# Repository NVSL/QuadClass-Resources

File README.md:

# The Quadcopter Class

Welcome to CSE176e Robotic System Design and Implementation (AKA, the Quadcopter Class).

This repo serves an the homepage for the course labs. It contains all
the lab write ups and several resources you will use throughout the
course.

- `labs` has all the labs. The write ups reference the starter repos they use.
- `Fusion 360` has the pre-built parts library, CAM files, and design rule files to use with Fusion 360.
- `Lecture Slides` has slides that aren't part of any particular lab.

Please see the [course home page](https://sites.google.com/ucsd.edu/the-quadcopter-class/home) or the [class calendar](ohttps://docs.google.com/spreadsheets/d/1cgSJm-5A6JrrA-iNKX8d2A0SE1PBk1CwzLvdhLKHuWY/) for schedule, due dates, and other logistical issues.

## A Note About Software Tool Names

The PCB design software we use is called Fusion 360. It used to be known as "Eagle". I've mostly updated the course materials to reflect this change.  If you see "Eagle" you should think "Fusion 360".

## Overview

We are going to build remote-controlled quadcopters from scratch in 10 weeks.

The goals for the course are for you to learn how to design, assemble, and program a moderately complex electronic device. The device you will build is a small, remote-controlled quadcopter similar to this:

In particular, you'll learn and/or practice these skills/topics:

- Printed circuit board design
  - Implementing a spec
  - Leveraging reference designs
  - Interpreting data sheets
  - Selecting parts
- PCB Assembly
  - Concepts
  - Moderately advanced soldering
- Embedded Systems Programming
  - Real-time
  - Resource constrained
- Basic Sensor fusion
- Basic Control Theory

## Labs

There are 10 labs divided into four sections. Deadlines are on the course homepage.

The slides for each lab are in the directory with the lab description.

### PCB Design

1. [Introduction To Fusion 360](https://github.com/NVSL/QuadClass-Resources/tree/master/labs/Introduction-To-Eagle)
2. [Building Parts In Fusion 360](https://github.com/NVSL/QuadClass-Resources/tree/master/labs/Building-Parts-In-Eagle)
3. [Building The Quadcopter Schematic](https://github.com/NVSL/QuadClass-Resources/tree/master/labs/Building-The-Quadcopter-Schematic)
4. [Laying Out The Board](https://github.com/NVSL/QuadClass-Resources/tree/master/labs/Laying-Out-The-Board)
5. [Manufacturing The Board](https://github.com/NVSL/QuadClass-Resources/tree/master/labs/Manufacturing-The-Board)

### PCB Assembly

6. [Assembling A PCB](https://github.com/NVSL/QuadClass-Resources/tree/master/labs/Assembling-A-PCB)

### Software

7. [Programming The Hardware](https://github.com/NVSL/QuadClass-Resources/tree/master/labs/Programming-The-Hardware)
8. [Sensing and Control](https://github.com/NVSL/QuadClass-Resources/tree/master/labs/Sensing-And-Control)
<!-- 8. [Sensing and Filtering](https://github.com/NVSL/QuadClass-Resources/tree/master/labs/Sensing-And-Filtering)-->
<!-- 9. [Implementing PID](https://github.com/NVSL/QuadClass-Resources/tree/master/labs/Implementing-PID)-->

### Flight

9. [Flight](https://github.com/NVSL/QuadClass-Resources/tree/master/labs/Flight)
10. [Cleanup](https://github.com/NVSL/QuadClass-Resources/tree/master/labs/Cleanup)

## Lab Equipment

The course requires several pieces of equipment:

1. A remote control.
2. A PID test stand.
3. A quadcopter prototype.
4. Miscelleneous cables, parts, etc.

You will also build a quadcopter, which you can also keep.

### Keeping the Remote

You cannot keep the remote you used in class. However, I a limited number of older remote boards that you can have if you really want one. Please talk to me near the end of the course, if you are interested.

### Returning the Equipment

The PID test stand, flight control board, remote, and other miscelleneous equipment you borrow for the labs must be returned or replaced (modulo normal wear and tear) before I will assign you a grade in the course.

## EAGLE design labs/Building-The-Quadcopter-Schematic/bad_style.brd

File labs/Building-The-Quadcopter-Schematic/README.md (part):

# Assembling The Quadcopter Schematic

To be completed in pairs.

Check course schedule for the due dates.

## Skills to Learn

1. Design a schematic to match a written specification.
2. Integrate portions of a reference design into your schematic.
3. Read and understand key portions of part datasheets.

## Equipment, Supplies, and Software You Will Need

1. Create a team in eaglint. You _must_ do this before clicking the starter link below.
1. The repo you started in "Programming the Hardware Lab"
1. The `custom.lbr` library you built in previous lab, OR your cloud save for the custom library. From here on out, maintain copies of your libraries on the cloud.
1. Read through the [Fusion Tricks Page](../../Fusion-Tricks.md) and skim the [Autodesk docs](https://help.autodesk.com/view/fusion360/ENU/?guid=ECD-SCHEMATIC) that go over the design tools you will use this lab.

## Preliminaries

### Setting up Fusion360

The repo for this lab will evolve to hold all the hardware and software for your quadcopter for the remainder of the quarter.

Now would be a good time to start utilizing Fusion Teams. To get started, decide between you and your partner on whose `custom` library should be used. That person should locate the Team online manager in the Data panel on the left:

This will open up a web browser to manage your team. You can edit the name, invite your partner using their email, and have shared access to a cloud version of your library! Rename it as `custom_<name>` so that the versions from both team members can co-exist. If you run into issues with one partner's library, you can always import your other library into Fusion360, just be sure to maintain them using the cloud! You should not reference local versions of `.lbr` files, and you should only export them when you are ready to submit.

To clean up local copies of previously-used `.lbr` files, and to remove unnecessary third-party libraries, you can remove them using the library manager (make sure to keep your team's library in use):

Feel free to remove all libraries except for your `custom` team library from last lab.

### Dealing with GitHub and Fusion360

Both GitHub and Fusion360 provide a mechanism for you to collaborate with your partner on the design:

- Fusion360 requires you to keep all your design files in the cloud and it allows you to share your design with other members of your team. This means that you and you're partner will be working on the same files. This is reasonably convenient and deeply integrated into Fusion360.

- GitHub uses the clone/commit/push process you are familiar with.

These two mechanisms don't work especially well together, unfortunately. The main problem is that getting files in and out of Fusion360 so you can work with them in GitHub is a hassle during collaboration.

Here is what has worked reasonably well in the past:

1. Use Fusion360s collaboration mechanisms while working on your project. It saves intermediate versions, so you can always roll back.
2. Only export your work from Fusion360 and commit it to GitHub to run it through Eaglint and turn it in.

The last step is a still a bit of a pain, but Eaglint doesn't know how to communicate with Fusion360 (yet), so there's no other option.

### Make Fusion360 Easier to Use

By default, Fusion360 comes configured with a bunch of libraries that can make it hard to find the libraries we are using for this class. This is controlled by the directories Fusion360 is setup to look in for library and other files. You can change the directories by selecting `User->Preferences` (upper-right corner) and then selecting `General->Electronics->Directory`.

To keep Fusion happy and make it easier to access and update libraries in the cloud, remove all the local folders Fusion is configured to look in for libraries. For Design rules and CAM files, I suggest the following settings:

- Design Rules: `<path to>/QuadClass-Resources/Eagle/DRU`
- CAM Jobs: `<path to>/QuadClass-Resources/Eagle/CAM`

## Assembling the Schematic

You’ll build quadcopter in the cloud starting from a new Fusion360 electronics design called `quadcopter`. When creating this design, make sure to save it to the right team.

In this lab, you will create a schematic associated with this design, to be exported to the folder `hardware/quadcopter.sch`. Feel free to review [Lab 1](https://github.com/NVSL/QuadClass-Resources/tree/master/labs/Introduction-To-Eagle#exporting-files) for a refresher on exporting. You'll assemble the design by studying reference designs and the datasheets for the components you will use.

We will be sharing a library with you via the cloud called `quadparts_prebuilt_2022` located in `QuadClass-Resources\Eagle\lbr`. You will be reusing your `custom` library from last lab, and in this lab you will also create a new library called `LEDs`. These should be the only 3 libraries you use to assemble your schematic, Fusion360 comes with a bunch of built in libraries but they are off limits.

### General Schematic Style Guidelines

Here are the course style guidelines for schematics. Your schematics must adhere to these guidelines. If you don't, Eaglint will give warnings and we won’t accept the design.

1. All visible net and component names must not have “\$” in them. When Fusion360 automatically generates names for nets and components it includes “$”. This is fine if the name is not visible (e.g., on an anonymous wire between two components), but if you it shows up on your schematic, you should give it a nice name like `CTRL` or `SCL`.
2. By convention power supply symbols point up, and ground symbols point down. Neither should ever point to the side.
3. Nets should not cross each other unless they are electrically connected.
4. Nets should only be drawn at right angles.
5. Fusion360 embeds libraries in the `.sch` and `.brd` files. Make sure that you are keeping libraries up-to-date with `Library->Update...` or `Library->Update All`. We won’t accept designs with inconsistent libraries.
6. Include a frame around our schematic. Use device `FRAME_B_L`.
7. Use lines in `Info` layer to divide the frame into logically related regions (e.g., the IMU, the power supply, and the microcontroller). See the BBB schematic below for an example. Drawn nets shouldn’t cross these boundaries.
8. Use drawn nets connect components that are closely related (e.g., between the caps and the microcontroller in the BBB schematic)
9. Use named nets to connect separate “sub units” of your schematic. For instance, use drawn nets to connect all the capacitors to your IMU, but use named nets to connect your IMU to the microcontroller.
10. You should not use any libraries other than `quadparts_prebuilt_2022`, your `custom_*`, and your `LEDs` libraries.
11. Schematic symbols and wires should all be aligned to 0.05in grid (or, if you like, a 0.1in grid).
12. Labels for nets (created using the 'label' tool) should need to placed on the net they label. This means the label's location (which is marked with a gray '+') needs to be on top of a corner or end of the net. This guards against "drifting labels" that seem to be attached to another net.

### Selecting Parts

The `quadparts_prebuilt_2022` library has lots of parts in it, many of which you won't use. I've provided specific guidance about which options to select below. For resistors and capacitors, you need to use 0805 parts not the smaller and harder-to-place 0603 parts.  You should also avoid the resistor packs.  They are hard to place and solder.  If the resistor you need is not available in 0805, you'll need to create it.

### The Microcontroller

Here's the schematic for a board called the Basic Breakout Board (BBB). It uses the same microcontroller as your quadocpter, but it does not include the voltage regulator. It's the reference design for your microcontroller and the radio. The design also includes the 1x6-pin programming header you can see on the bottom of the FCB. YOu don't need to include that header in your design.

Why did I give a picture of what you need to build? Because reference designs are a very common practice in real PCB designs. The most reliable way to convey design requirements is to provide a working design. Why reinvent the wheel?

You should use the schematic as a guide for constructing the microcontroller portion of your schematic. Build it from parts from `quadparts_prebuilt_2022` libbrary:

1.  Use one of the `-BOARD...` variants for the antenna. There's a left and right-handed version. Depending on your ultimate board design, you might want one or the other.
2.  `B1` is a 'balun'. Pay attention to the pin numbers.
3.  Use the `0.45x0.45` button.
4.  Replace one of the green LEDs with your red LED.
5.  You can use either variant for the `AVR_SPI...` header. The surfacemount one takes up more space (see it on your remote, under the LCD). The throughole one is more compact.
6.  You won't need the FTDI portion of the design.
7.  Do not connect the power pin on the ISP programmer/Bootloader header.
8.  Reference designs use different voltages from what you may want to use. Use 3V instead of 3V3.

You might notice that some of the symbols for the parts seem backwards. This is because they are 'mirrored'. There's a mirror tool or your can mirror parts by editing their properties with the `info` tool.

There are some changes you will need to make to this schematic based on what's required by the other components. This is just a starting point for your circuit.

If you have questions about the parts attached directly to the microcontroller (including the radio), the first place to turn is the microcontroller datasheet.

### Programming Header

Your quad will use a 4-pin programming header to load code into the MCU. You won't need the FTDI portion of the reference design. It's a little fancy since it allows you to insert the cable from either top of the board _or_ the bottom. To this end, use the `-FEMALE-SMD-BOTTOM-ENTRY` part from `quadparts_prebuilt_2022`. The four signals must appear in this order:

1.  Serial TX
2.  Serial RX
3.  GND
4.  Reset

These are a subset of the signals that connect to the FTDI header in the microcontroller reference design. You don't need the FTDI header. Note that you do need the 0.1uF capacitor between the reset line and the reset pin on the programming header.

### The IMU

The IMU datasheet contains all the information you will need to use connect the IMU to the microcontroller. A few things to keep in mind:

1. The IMU datasheet is not the best. If something doesn't make sense search the pdf.
2. There are actually two logical devices in this package: the accelerometer/gyroscope (referred to as 'A/G' in the datasheet ).
3. Both devices will operate in I2C mode only and connect to microcontroller via I2C, so you can ignore the stuff in the data sheet that refers to SPI.
4. The IMU has different connection modes. Follow connection mode 1 for your design, which is referred in `7.1 LSM6DSO electrical connections in Mode 1`, page 35.
5. You must follow all the recommendations regarding external capacitors attached the IMU, also known as decoupling capacitors.
6. You will need to take care of configuring the IMU's I2C addresses. Read section `5.1.1 I2C Serial interface`, pages 17 and 18, to determine which I2C address you can use. Use `Table 19. Internal pin status`, page 38 column Mode 1, to figure out which pin is dedicated for selecting the I2C address. You choose which address you want to use, but the address you choose needs to be reflected in your, otherwise your software won't be able to communicate with the IMU.
7. We aren't using the interrupt features, so you can leave `INT1` and `INT2` disconnected.
8. Power supply voltage (`Vdd`) and IO voltage (`Vdd_IO`) will be 3.0V in our design, so connect both to `3V`.
9. Connect `SDX` and `SCX` to GND.
10. We want the I2C to be always enabled. Determine if `CS` (Chip Select) should be connected to 3V (1) or GND (0) by reading "Table 1. Pin Description" in the IMU datasheet. Keep in mind that the IMU can work in diferent modes, we want mode 1. 

A thing to know about datasheets: They almost always (although, frustratingly, not always) tell you everything you need to know. They don't, however, make it easy. You need to read carefully and thoroughly. You can't skim the datasheet and expect to know the details of how to connect each of the pins to configure the IMU properly. You actually need to read through the tables and the text, there are specific answers to most questions you might have in there. Most facts appear exactly once in the datasheet -- it will be written in text or a table, but not both.

### The I2C Bus

Your MCU will communicate with the IMU via I2C. This means you must connect the IMU to the MCU via the `SDA` and `SCL` lines. You should "pull up" these lines to `3V` by connecting them to `3V` using 10kOhm resistors. Read section `7.1 LSM6DSO electrical connections in Mode 1`, page 35, to know how the pull-up resistos must be connected.

### The Motor Driver

Here's a picture of the motor driver circuit:

Build four copies to drive the four motors you'll need. All the parts you need are in `quadparts_prebuilt_2022` or your `custom` libraries.

1. Use the `-SMD-SOD123` diode in the library.
2. Use the `-MOLEX-SMD` variant of the `MOTOR_PADS_GND` device of the motor connector.
3. Use your MOSFET, of course.

The ground pin on the motor pads is not actually connected to the motor. It just goes to the metal "feet" that hold the connector down. You can see them on your FCB.

You'll need to connect the PWM control lines to suitable pins on the microcontroller. The suitable pins are marked with "~" on microcontroller's schematic symbol.

You need to include one 47uF decoupling capacitor between `VBAT` and `BAT_GND` (just one; not one per motor). It's to help absorb switching noise from the motors. Note that 47uF capacitor in the library is polarized. In the schematic the curved "plate" on the symbol should be connected to ground.

### The Power Supply

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
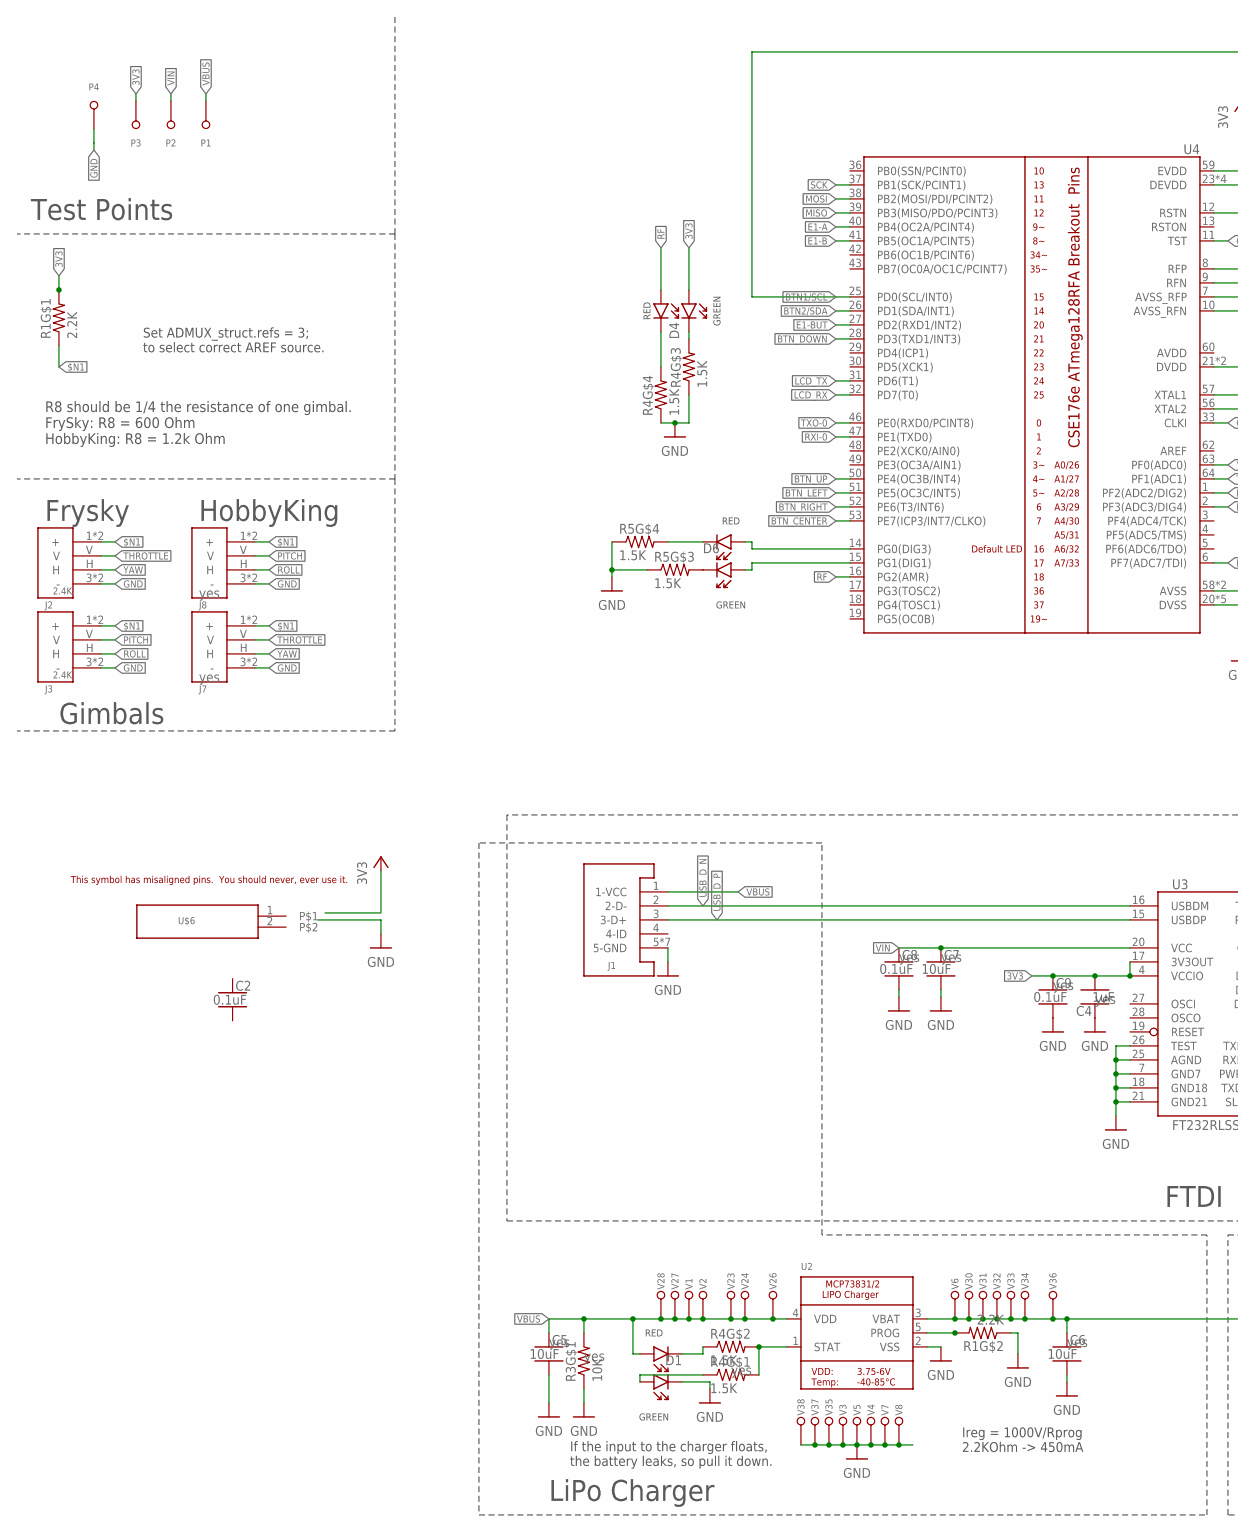
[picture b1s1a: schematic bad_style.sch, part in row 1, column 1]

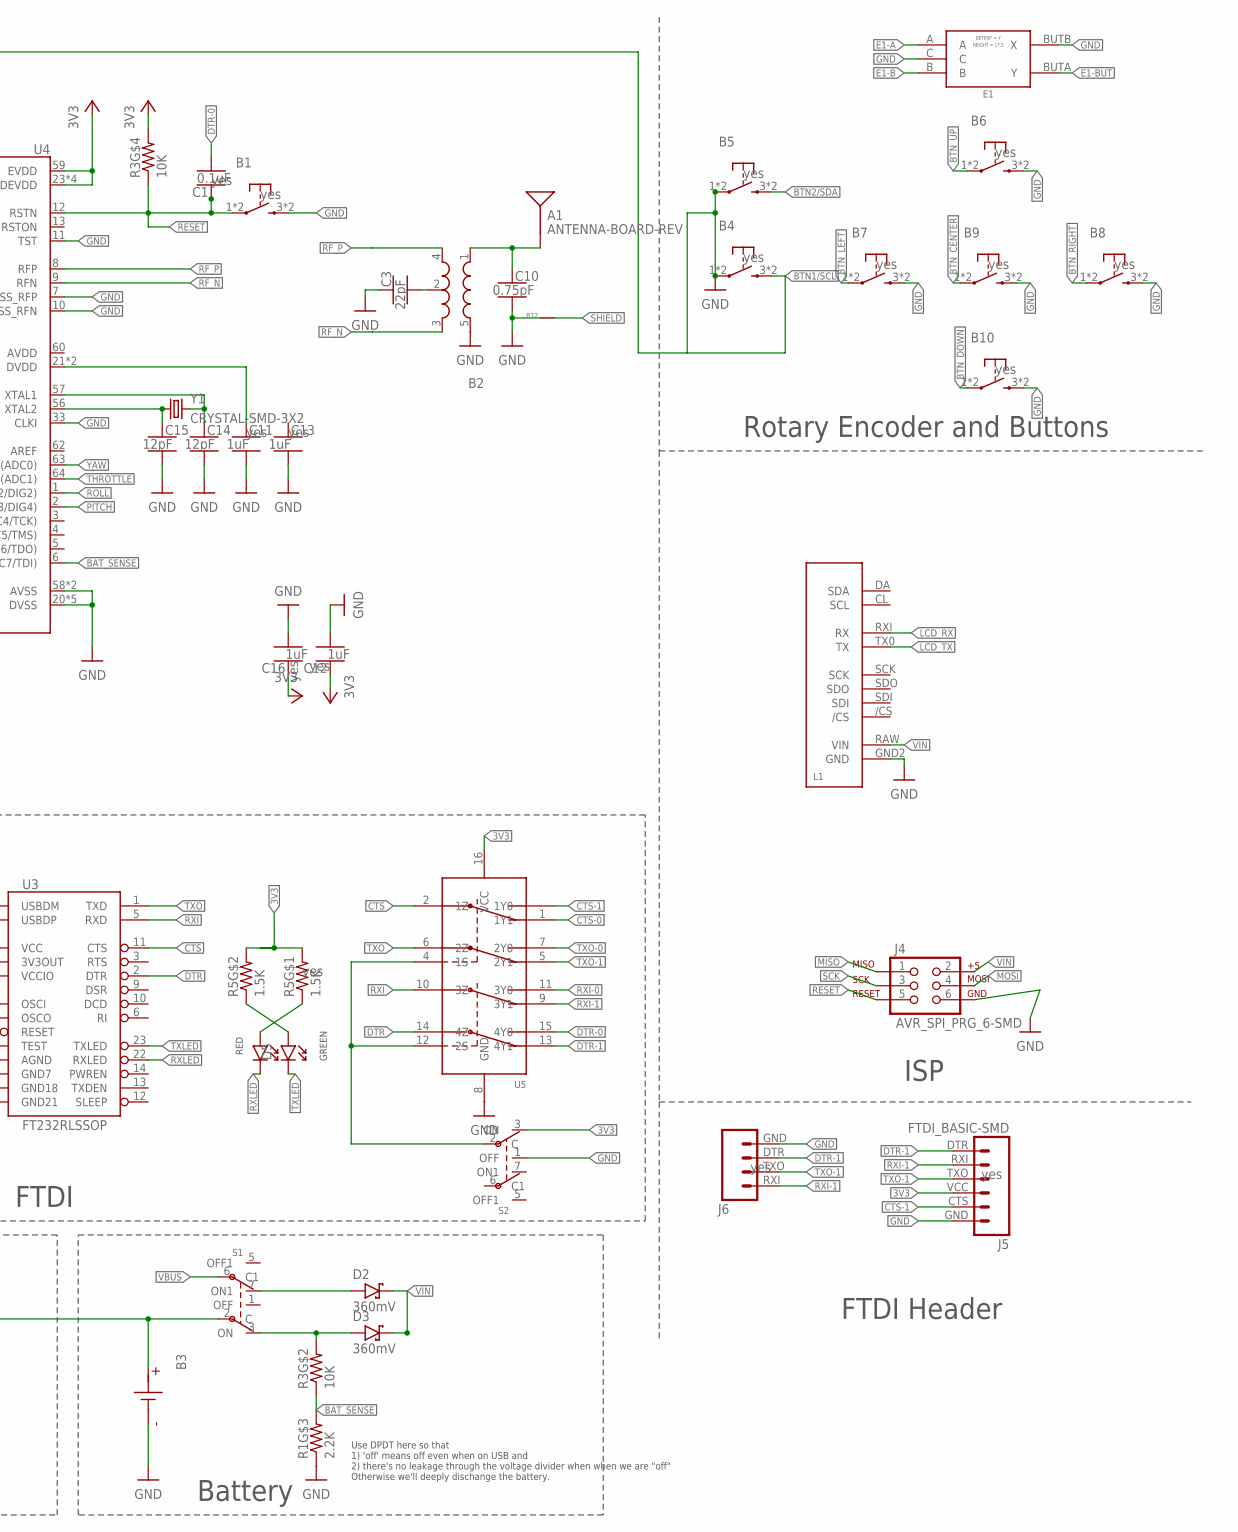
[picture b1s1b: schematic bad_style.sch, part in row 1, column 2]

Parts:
A1: ANTENNA-BOARD-REV; ANT_PCB_2.4GHZ_NRF8001_1.6MM_1OZ_REV
B1, B4, B5, B6, B7, B8, B9, B10: PUSHBUTTON_-4.5X4.5; 4.5MM_TACTILE_SWITCH_TL3305AF160QG
B2: BALUN0805; BALUN
B3: BATTERY-SMD; MOLEX-BATTERY-CONNECTOR-SMD-51005-2P
B12: NET_BRIDGE
C1, C2, C8, C9: 0.1uF; CAPC1608X100
C3: 22pF; CAPC1608X100
C4, C11, C12, C13, C16: 1uF; CAPC1608X100
C5, C6, C7: 10uF; CAPC1608X100
C10: 0.75pF; CAPC1608X100
C14, C15: 12pF; CAPC1608X100
D1, D4, D5, D6: LED-2X-GREEN/RED-1.6X1.5MM; LED-2X-LITE-ON-1.6MMX1.5MM
D2, D3: 360mV; SODFL3516X96
E1: ROTARY-ENCODER-W/BUTTON-BOURNS-PEC12R-4217F; BOURNS-PEC12R
J1: USB-MICROA-AMPHENOL-10118192-0001LF; USB-MICROA-10118192-0001LF
J2, J3: 2.4K; JST-13-PTH
J4: AVR_SPI_PRG_6-SMD; 2X3-SMD
J5: FTDI_BASIC-SMD; FTDI-BASIC-SMD
J6: FTDI-4PIN-RIGHT-ANGLE-SMD; HEADER-2X2-0.1IN-MALE-RIGHT-ANGLE-SMD
J7, J8: FRSKY-GIMBAL-2X-SERVO-SMD; 2X-SERVO-SMD
L1: SPARKFUN_SERLCD_SERIAL_REDUCED-SMD; SPARKFUN_SERLCD_16X2_REDUCED_SMD
P1, P2, P3, P4: TEST-POINT; TEST-POINT-KEYSTONE-5000
R1: 2.2K; RESCAXS50P200X100X45-8
R3: 10K; RESCAXS50P200X100X45-8
R4, R5: 1.5K; RESCAXS50P200X100X45-8
S1, S2: SWITCH-DPDT-300MA-6V-SMD; JS202011JCQN
U2: MCP73831T-2ACI/OT; SOT23-5
U3: FT232RLSSOP; SSOP28DB
U4: ATMEGA128RFA1; QFN-64
U5: DPDT-X2; SOP65P640X110-16
U$6: DONT_USE; SCREW-TERMINAL-1X2-2.54MM
V1, V2, V3, V4, V5, V6, V7, V8, V23, V24, V26, V27, V28, V30, V31, V32, V33, V34, V35, V36, V37, V38: LOCKED-VIA-0.2; VIA-0.2MM
Y1: CRYSTAL-SMD-3X2; OSCCC320X250X85

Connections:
3V3: C4.2, C9.1, C12.1, C16.1, D4.A1, J5.VCC (4), P3.T, R1.5 (2), R3.8 (2), R5.5 (2), R5.6 (2), S2.3 (ON), U3.4 (VCCIO), U3.17 (3V3OUT), U4.23 (DEVDD), U4.34 (DEVDD), U4.44 (DEVDD), U4.54 (DEVDD), U4.59 (EVDD), U5.16 (VCC)
$N1: J2.1 (+), J2.4 (+), J3.1 (+), J3.4 (+), J7.1 (+), J7.4 (+), J8.1 (+), J8.4 (+), R1.4 (1)
ANTENNA: A1.FEED, B2.1 (IN), C10.1
BAT_SENSE: R1.7 (2), R3.3 (1), U4.6 (PF7(ADC7/TDI))
BCAP: B2.2 (GND), C3.2
BPOS: B3.P, C6.1, S1.2 (C), U2.3 (VBAT), V6.P1, V30.P1, V31.P1, V32.P1, V33.P1, V34.P1, V36.P1
BTN1/SCL: B4.3 (2), B4.4 (2), U4.25 (PD0(SCL/INT0))
BTN2/SDA: B5.3 (2), B5.4 (2), U4.26 (PD1(SDA/INT1))
BTN_CENTER: B9.1, B9.2 (1), U4.53 (PE7(ICP3/INT7/CLKO))
BTN_DOWN: B10.1, B10.2 (1), U4.28 (PD3(TXD1/INT3))
BTN_LEFT: B7.1, B7.2 (1), U4.51 (PE5(OC3C/INT5))
BTN_RIGHT: B8.1, B8.2 (1), U4.52 (PE6(T3/INT6))
BTN_UP: B6.1, B6.2 (1), U4.50 (PE4(OC3B/INT4))
CLK_NEG: C15.1, U4.56 (XTAL2), Y1.1
CLK_POS: C14.1, U4.57 (XTAL1), Y1.3 (2)
CTS: U3.11 (CTS), U5.2 (1Z)
CTS-0: U5.3 (1Y0)
CTS-1: J5.CTS (5), U5.1 (1Y1)
DTR: U3.2 (DTR), U5.14 (4Z)
DTR-0: C1.2, U5.15 (4Y0)
DTR-1: J5.DTR (1), J6.DTR (3), U5.13 (4Y1)
E1-A: E1.A, U4.40 (PB4(OC2A/PCINT4))
E1-B: E1.B, U4.41 (PB5(OC1A/PCINT5))
E1-BUT: E1.BUTA (Y), U4.27 (PD2(RXD1/INT2))
GND: B1.3 (2), B1.4 (2), B2.5 (GND), B3.G (N), B3.G2 (N), B3.G3 (N), B4.1, B4.2 (1), B5.1, B5.2 (1), B6.3 (2), B6.4 (2), B7.3 (2), B7.4 (2), B8.3 (2), B8.4 (2), B9.3 (2), B9.4 (2), B10.3 (2), B10.4 (2), B12.P1, C3.1, C4.1, C5.2, C6.2, C7.2, C8.2, C9.2, C10.2, C11.2, C12.2, C13.2, C14.2, C15.2, C16.2, D1.C1, E1.BUTB (X), E1.C, J1.5 (5-GND), J1.6 (5-GND), J1.7 (5-GND), J1.8 (5-GND), J1.9 (5-GND), J1.10 (5-GND), J1.11 (5-GND), J2.3 (-), J2.6 (-), J3.3 (-), J3.6 (-), J4.6, J5.GND (6), J6.GND (4), J7.3 (-), J7.6 (-), J8.3 (-), J8.6 (-), L1.GND2 (GND), P4.T, R1.2 (1), R1.3 (1), R3.4 (1), R4.1, R4.2 (1), R5.1, R5.2 (1), S2.1 (OFF), U2.2 (VSS), U3.7 (GND7), U3.18 (GND18), U3.21 (GND21), U3.25 (AGND), U3.26 (TEST), U4.7 (AVSS_RFP), U4.10 (AVSS_RFN), U4.11 (TST), U4.20 (DVSS), U4.24 (DVSS), U4.33 (CLKI), U4.35 (DVSS), U4.45 (DVSS), U4.55 (DVSS), U4.58 (AVSS), U4.61 (AVSS), U5.8 (GND), V3.P1, V4.P1, V5.P1, V7.P1, V8.P1, V35.P1, V37.P1, V38.P1
LCD_RX: L1.RXI (RX), U4.32 (PD7(T0))
LCD_TX: L1.TX0 (TX), U4.31 (PD6(T1))
MISO: J4.1, U4.39 (PB3(MISO/PDO/PCINT3))
MOSI: J4.4, U4.38 (PB2(MOSI/PDI/PCINT2))
unnamed: D1.A1, R4.4 (1)
unnamed: D1.C2, R4.3 (1)
unnamed: D5.A1, R5.3 (1)
unnamed: D6.C2, R5.8 (2)
unnamed: D6.C1, R5.7 (2)
unnamed: D4.C1, R4.7 (2)
unnamed: D5.A2, R5.4 (1)
unnamed: D6.A2, U4.14 (PG0(DIG3))
unnamed: D6.A1, U4.15 (PG1(DIG1))
unnamed: R4.5 (2), R4.6 (2), U2.1 (STAT)
unnamed: R1.6 (2), U2.5 (PROG)
unnamed: D4.C2, R4.8 (2)
unnamed: D2.2 (A), S1.7 (ON1)
unnamed: C11.1, U4.21 (DVDD), U4.22 (DVDD)
PITCH: J3.V, J8.V, U4.2 (PF3(ADC3/DIG4))
PROG_SEL: S2.2 (C), U5.4 (1S), U5.12 (2S)
RESET: B1.1, B1.2 (1), C1.1, J4.5, R3.1, U4.12 (RSTN)
RF: D4.A2, U4.16 (PG2(AMR))
RF_N: B2.3 (OUT2), U4.9 (RFN)
RF_P: B2.4 (OUT1), U4.8 (RFP)
ROLL: J3.H, J8.H, U4.1 (PF2(ADC2/DIG2))
RXI: U3.5 (RXD), U5.10 (3Z)
RXI-0: U4.47 (PE1(TXD0)), U5.11 (3Y0)
RXI-1: J5.RXI (2), J6.RXI (1), U5.9 (3Y1)
RXLED: D5.C2, U3.22 (RXLED)
SCK: J4.3, U4.37 (PB1(SCK/PCINT1))
SHIELD: B12.P2
THROTTLE: J2.V, J7.V, U4.64 (PF1(ADC1))
TXLED: D5.C1, U3.23 (TXLED)
TXO: U3.1 (TXD), U5.6 (2Z)
TXO-0: U4.46 (PE0(RXD0/PCINT8)), U5.7 (2Y0)
TXO-1: J5.TXO (3), J6.TXO (2), U5.5 (2Y1)
USB_D_N: J1.2 (2-D-), U3.16 (USBDM)
USB_D_P: J1.3 (3-D+), U3.15 (USBDP)
VBAT: D3.2 (A), R3.6 (2), S1.3 (ON)
VBUS: C5.1, D1.A2, J1.1 (1-VCC), P1.T, R3.5 (2), S1.6 (C1), U2.4 (VDD), V1.P1, V2.P1, V23.P1, V24.P1, V26.P1, V27.P1, V28.P1
VIN: C7.1, C8.1, D2.1 (C), D3.1 (C), J4.2, L1.RAW (VIN), P2.T, U3.20 (VCC)
YAW: J2.H, J7.H, U4.63 (PF0(ADC0))

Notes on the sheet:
Ireg = 1000V/Rprog 2.2KOhm -> 450mA
LiPo Charger
Test Points
Frysky
HobbyKing
Rotary Encoder and Buttons
Battery
ISP
FTDI Header
Set ADMUX_struct.refs = 3; to select correct AREF source.
Gimbals
R8 should be 1/4 the resistance of one gimbal. FrySky: R8 = 600 Ohm HobbyKing: R8 = 1.2k Ohm
If the input to the charger floats, the battery leaks, so pull it down.
FTDI
Use DPDT here so that 1) 'off' means off even when on USB and 2) there's no leakage through the voltage divider when when we are "off" Otherwise we'll deeply dischange the battery.

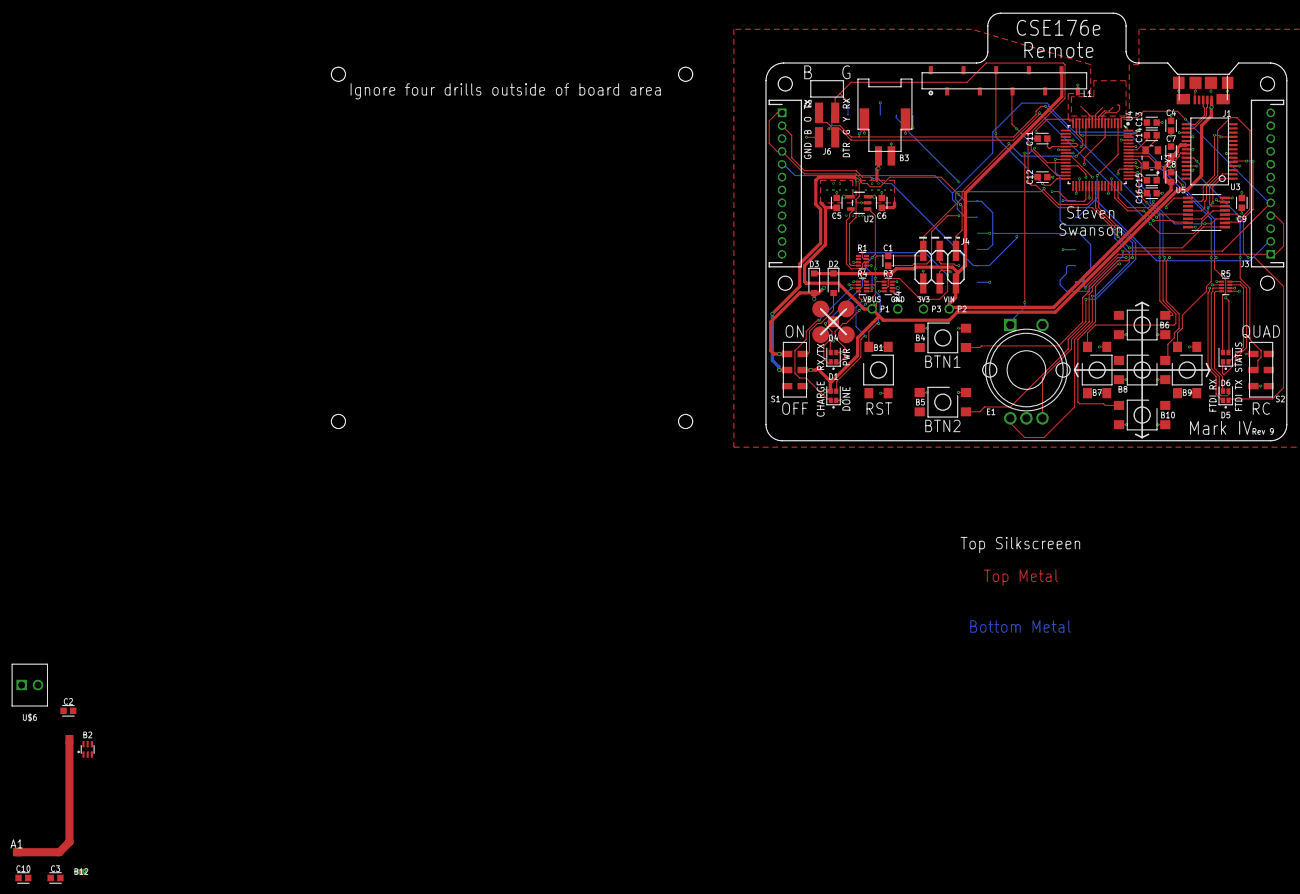
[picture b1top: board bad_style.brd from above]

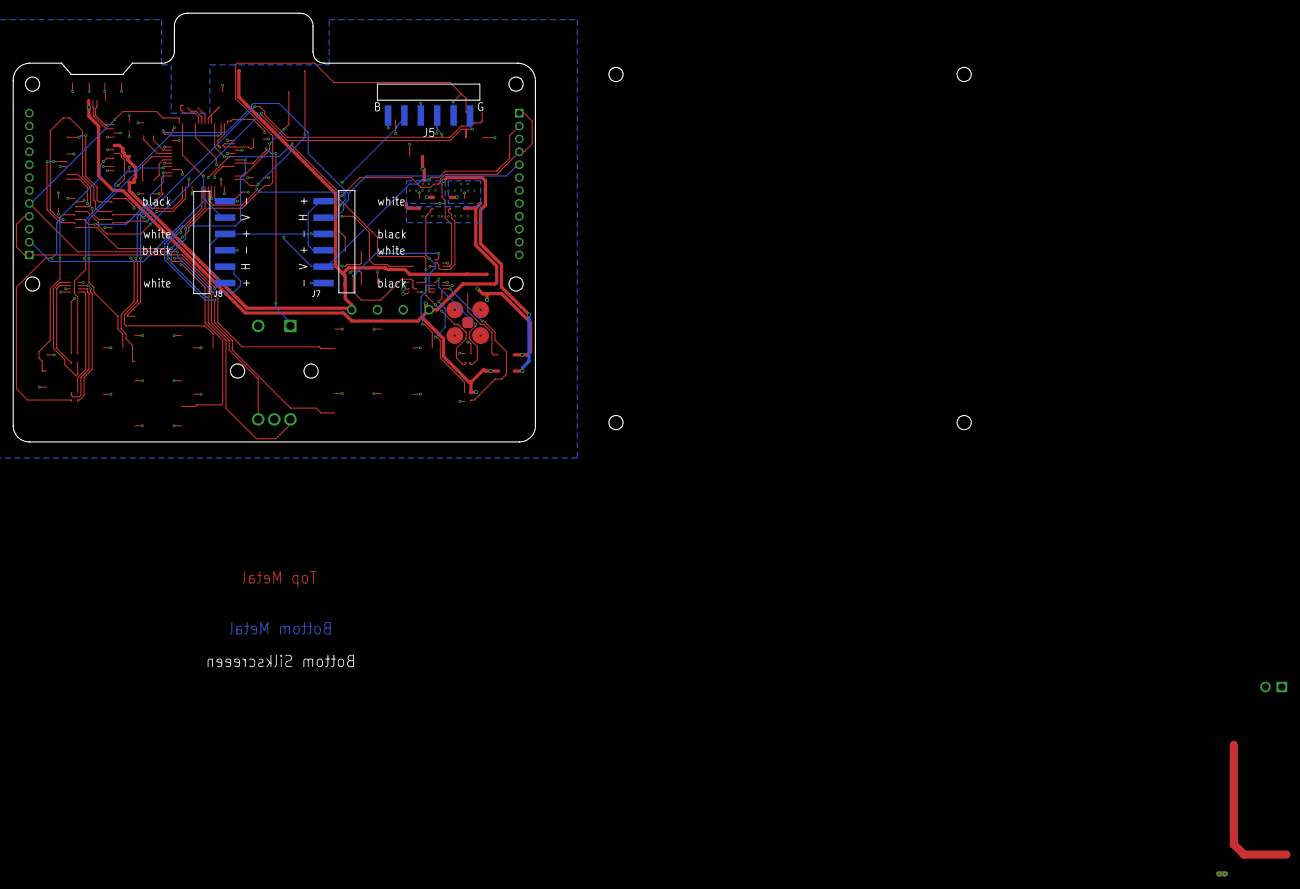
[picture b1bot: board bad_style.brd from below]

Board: 4 copper layers, 81.0 x 66.5 mm, 89 parts (3 on the bottom side), 65 nets.

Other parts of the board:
E$1, E$2: FRSKY-TARANIS-GIMBAL
U$1: 700MAH-BATTERY
U$2: QUADCLASS_LOGO_SMALL
U$3: LAYER_LABELS
U$4: 375MAH-BATTERY
U$5: 600MAH-BATTERY

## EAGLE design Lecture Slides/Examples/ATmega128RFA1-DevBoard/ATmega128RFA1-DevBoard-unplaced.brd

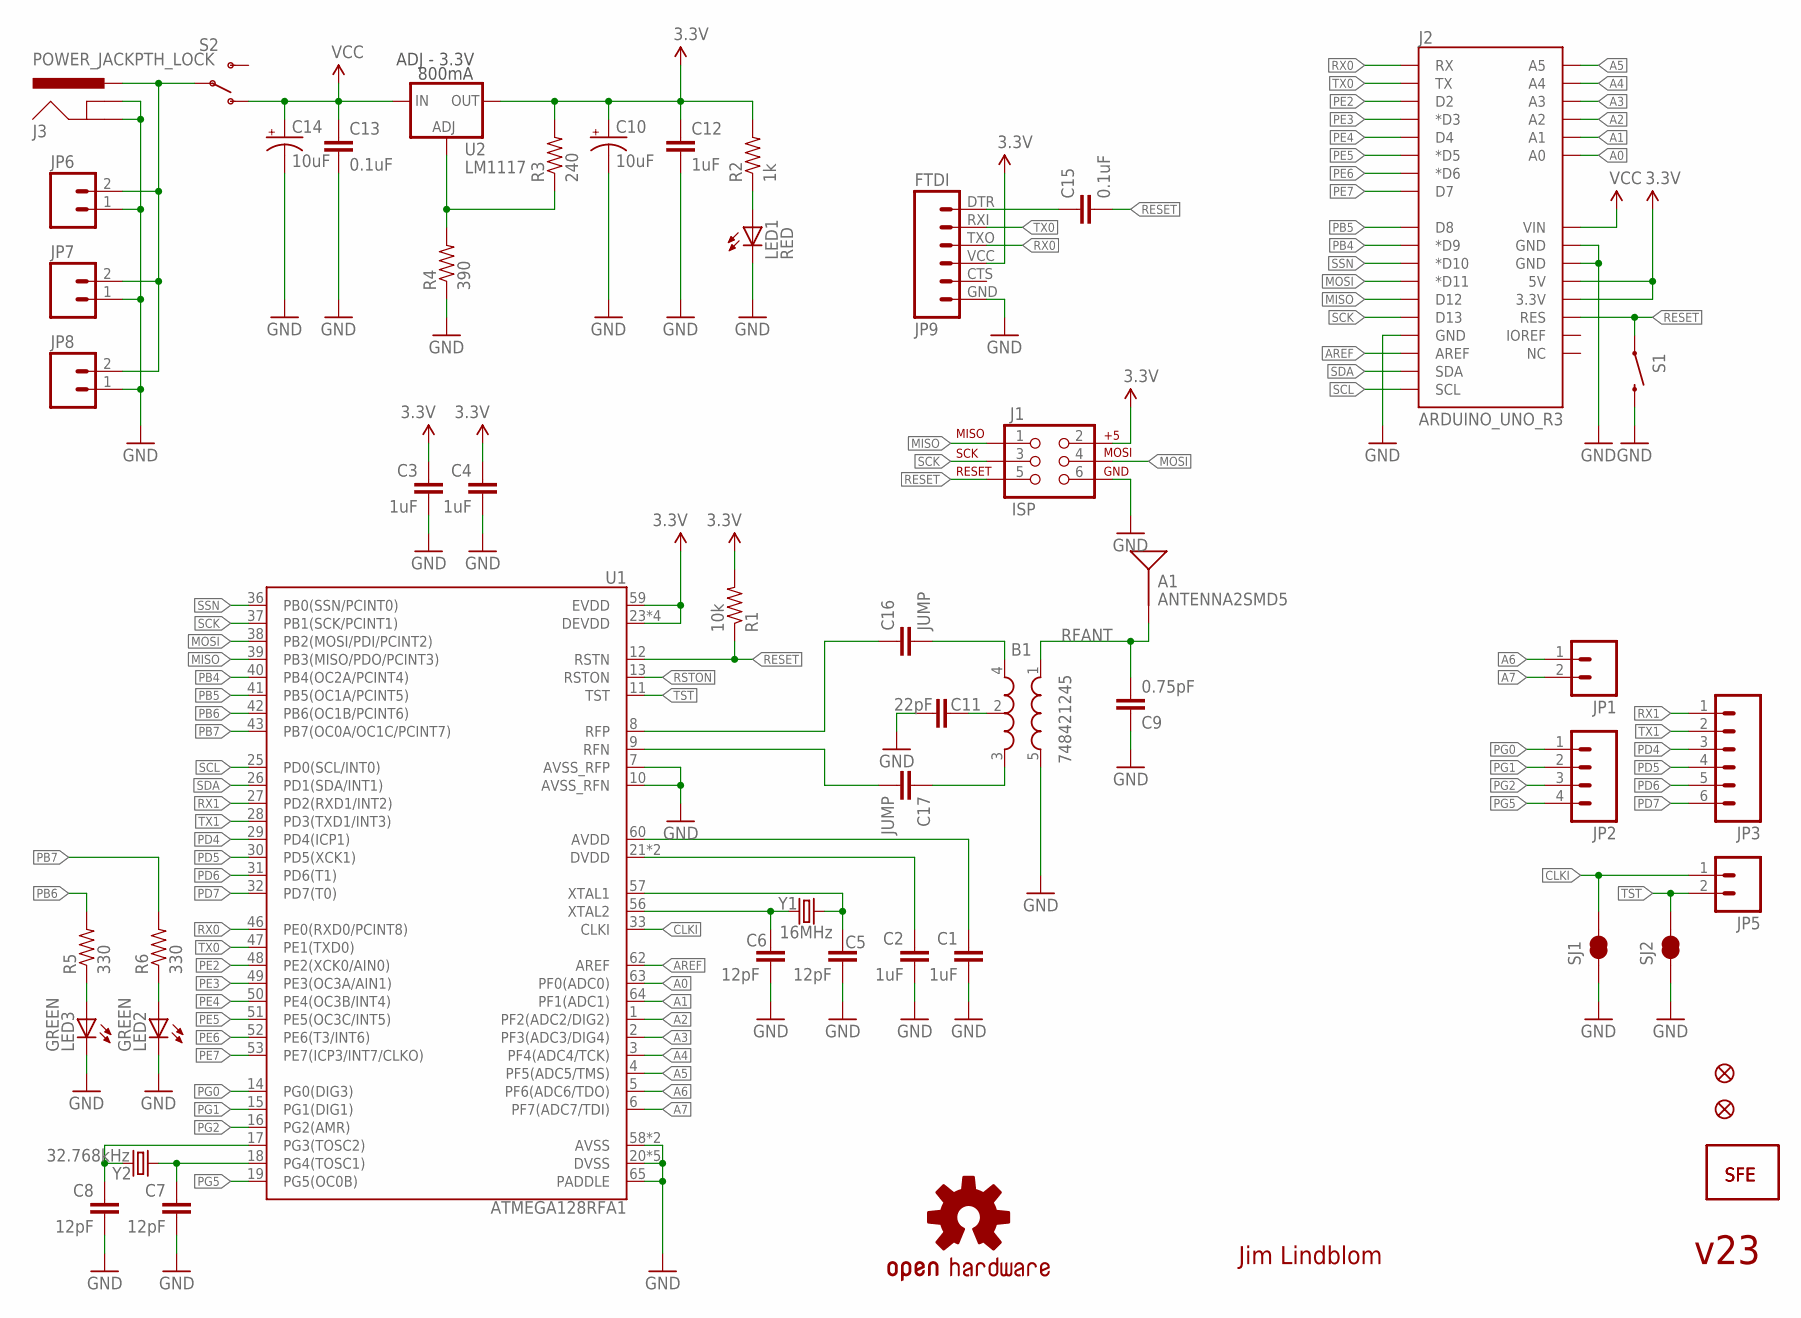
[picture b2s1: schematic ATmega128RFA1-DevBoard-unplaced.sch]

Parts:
A1: ANTENNA2SMD5; ANTENNA-CHIP5
B1: 748421245; BALUN
C1, C2, C3, C4, C12: 1uF; 0402-CAP
C5, C6, C7, C8: 12pF; 0402-CAP
C9: 0.75pF; 0402-CAP
C10, C14: 10uF; EIA3216
C11: 22pF; 0402-CAP
C13, C15: 0.1uF; 0402-CAP
C16, C17: JUMP; 0402-CAP
FID1, FID2: FIDUCIALUFIDUCIAL; MICRO-FIDUCIAL
J1: ISP; 2X3-NS
J2: ARDUINO_UNO_R3
J3: POWER_JACKPTH_LOCK; POWER_JACK_PTH_LOCK
JP1, JP5, JP7: M021X02_NO_SILK; 1X02_NO_SILK
JP2: M041X04_NO_SILK; 1X04_NO_SILK
JP3: M06SIP-NS; 1X06_NS
JP4, JP10: LOGO-SFENEW; SFE-NEW-WEBLOGO
JP6: M02JST-PTH-2; JST-2-PTH
JP8: M023.5MM-NO_SILK; SCREWTERMINAL-3.5MM-2-NS
JP9: FTDI; FTDI_BASIC
LED1: RED; LED-0603
LED2, LED3: GREEN; LED-0603
R1: 10k; 0402-RES
R2: 1k; 0402-RES
R3: 240; 0402-RES
R4: 390; 0402-RES
R5, R6: 330; 0402-RES
S1: SWITCH-MOMENTARY-2SMD; TACTILE_SWITCH_SMD
S2: SWITCH-SPST-SMD-A
SJ1, SJ2: SOLDERJUMPERTRACE; SJ_2S-TRACE
U1: ATMEGA128RFA1; QFN-64
U2: LM1117; SOT223
U$1: OSHW-LOGOS; OSHW-LOGO-S
Y1: 16MHz; CRYSTAL-SMD-5X3
Y2: 32.768kHz; CRYSTAL-32KHZ-SMD

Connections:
3.3V: C3.1, C4.1, C10.A (+), C12.1, J1.2, J2.3.3V, J2.5V, JP9.VCC (4), R1.2, R2.2, R3.2, U1.23 (DEVDD), U1.34 (DEVDD), U1.44 (DEVDD), U1.54 (DEVDD), U1.59 (EVDD), U2.2 (OUT)
A0: J2.A0, U1.63 (PF0(ADC0))
A1: J2.A1, U1.64 (PF1(ADC1))
A2: J2.A2, U1.1 (PF2(ADC2/DIG2))
A3: J2.A3, U1.2 (PF3(ADC3/DIG4))
A4: J2.A4, U1.3 (PF4(ADC4/TCK))
A5: J2.A5, U1.4 (PF5(ADC5/TMS))
A6: JP1.1, U1.5 (PF6(ADC6/TDO))
A7: JP1.2, U1.6 (PF7(ADC7/TDI))
AREF: J2.AREF, U1.62 (AREF)
AVDD: C1.1, U1.60 (AVDD)
CLKI: JP5.1, SJ1.2, U1.33 (CLKI)
DTR: C15.1, JP9.DTR (1)
DVDD: C2.1, U1.21 (DVDD), U1.22 (DVDD)
FB: R3.1, R4.2, U2.1 (ADJ)
GND: B1.5 (GND), C1.2, C2.2, C3.2, C4.2, C5.2, C6.2, C7.2, C8.2, C9.1, C10.C (-), C11.2, C12.2, C13.2, C14.C (-), J1.6, J2.GND@0 (GND), J2.GND@1 (GND), J2.GND@2 (GND), J3.GND, J3.GNDBREAK, JP6.1, JP7.1, JP8.1, JP9.GND (6), LED1.C, LED2.C, LED3.C, R4.1, S1.3 (2), SJ1.1, SJ2.1, U1.7 (AVSS_RFP), U1.10 (AVSS_RFN), U1.20 (DVSS), U1.24 (DVSS), U1.35 (DVSS), U1.45 (DVSS), U1.55 (DVSS), U1.58 (AVSS), U1.61 (AVSS), U1.65 (PADDLE)
MISO: J1.1, J2.D12, U1.39 (PB3(MISO/PDO/PCINT3))
MOSI: J1.4, J2.D11 (*D11), U1.38 (PB2(MOSI/PDI/PCINT2))
unnamed: LED1.A, R2.1
unnamed: C5.1, U1.57 (XTAL1), Y1.3 (2)
unnamed: C6.1, U1.56 (XTAL2), Y1.1
unnamed: C7.1, U1.18 (PG4(TOSC1)), Y2.X1 (1)
unnamed: C8.1, U1.17 (PG3(TOSC2)), Y2.X2 (2)
unnamed: B1.2 (GND), C11.1
unnamed: LED3.A, R5.1
unnamed: J3.PWR, JP6.2, JP7.2, JP8.2, S2.2
unnamed: B1.4 (OUT1), C16.2
unnamed: B1.3 (OUT2), C17.1
unnamed: LED2.A, R6.1
PB4: J2.D9 (*D9), U1.40 (PB4(OC2A/PCINT4))
PB5: J2.D8, U1.41 (PB5(OC1A/PCINT5))
PB6: R5.2, U1.42 (PB6(OC1B/PCINT6))
PB7: R6.2, U1.43 (PB7(OC0A/OC1C/PCINT7))
PD4: JP3.3, U1.29 (PD4(ICP1))
PD5: JP3.4, U1.30 (PD5(XCK1))
PD6: JP3.5, U1.31 (PD6(T1))
PD7: JP3.6, U1.32 (PD7(T0))
PE2: J2.D2, U1.48 (PE2(XCK0/AIN0))
PE3: J2.D3 (*D3), U1.49 (PE3(OC3A/AIN1))
PE4: J2.D4, U1.50 (PE4(OC3B/INT4))
PE5: J2.D5 (*D5), U1.51 (PE5(OC3C/INT5))
PE6: J2.D6 (*D6), U1.52 (PE6(T3/INT6))
PE7: J2.D7, U1.53 (PE7(ICP3/INT7/CLKO))
PG0: JP2.1, U1.14 (PG0(DIG3))
PG1: JP2.2, U1.15 (PG1(DIG1))
PG2: JP2.3, U1.16 (PG2(AMR))
PG5: JP2.4, U1.19 (PG5(OC0B))
RESET: C15.2, J1.5, J2.RES, R1.1, S1.1, U1.12 (RSTN)
RFANT: A1.FEED, B1.1 (IN), C9.2
RFN: C17.2, U1.9 (RFN)
RFP: C16.1, U1.8 (RFP)
RSTON: U1.13 (RSTON)
RX0: J2.RX, JP9.TXO (3), U1.46 (PE0(RXD0/PCINT8))
RX1: JP3.1, U1.27 (PD2(RXD1/INT2))
SCK: J1.3, J2.D13, U1.37 (PB1(SCK/PCINT1))
SCL: J2.SCL, U1.25 (PD0(SCL/INT0))
SDA: J2.SDA, U1.26 (PD1(SDA/INT1))
SSN: J2.D10 (*D10), U1.36 (PB0(SSN/PCINT0))
TST: JP5.2, SJ2.2, U1.11 (TST)
TX0: J2.TX, JP9.RXI (2), U1.47 (PE1(TXD0))
TX1: JP3.2, U1.28 (PD3(TXD1/INT3))
VCC: C13.1, C14.A (+), J2.VIN, S2.1 (O), U2.3 (IN)

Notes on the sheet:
Jim Lindblom
800mA
ADJ - 3.3V
v23

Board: 2 copper layers, 52 parts (0 on the bottom side), 61 nets, no tracks yet.

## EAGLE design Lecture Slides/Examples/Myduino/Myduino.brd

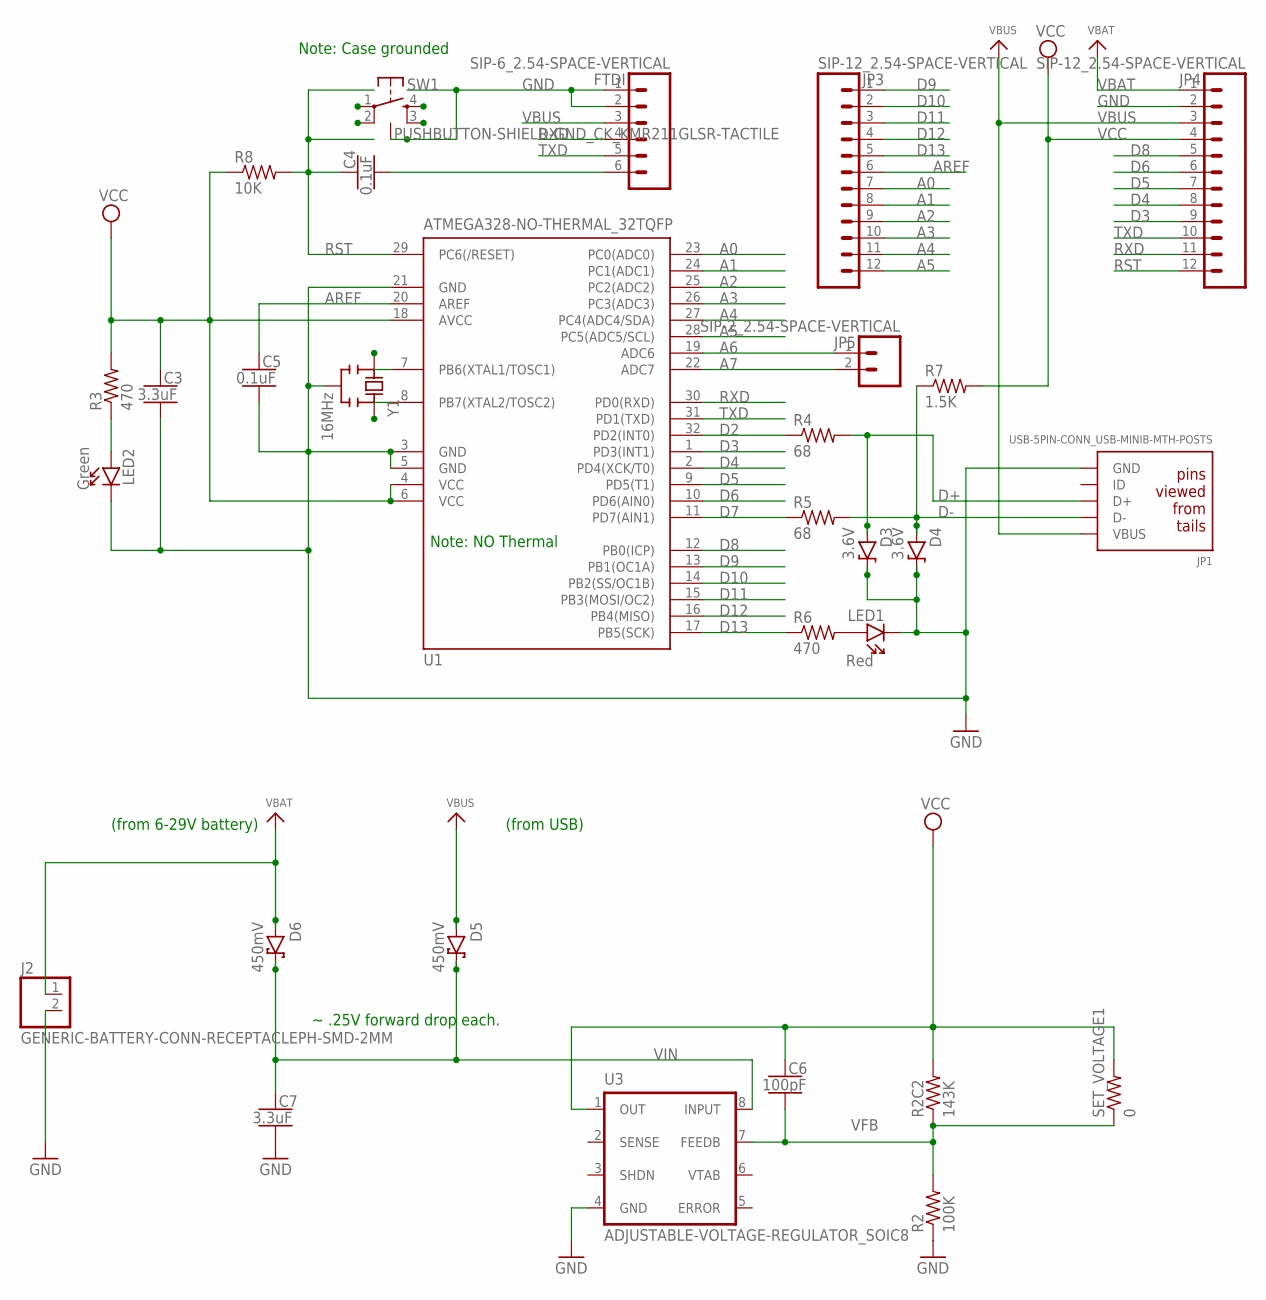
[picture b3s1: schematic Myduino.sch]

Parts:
C3, C7: 3.3uF; CAPC2012X140_HS
C4, C5: 0.1uF; CAPRB500W53L600T350H600_HS
C6: 100pF; CAPRB500W53L550T250H550_HS
D3, D4: 3.6V; DIOAD1660W102L890D370_HS
D5, D6: 450mV; DIOAD1125W78L520D270_HS
FTDI: SIP-6_2.54-SPACE-VERTICAL; HDRV6W63P254_6X1_1524X254H838; MPN TSW-150-07-T-S
J2: GENERIC-BATTERY-CONN-RECEPTACLEPH-SMD-2MM; JST_S2B-PH-SM4-TB; MPN S2B-PH-SM4-TB(LF)(SN)
JP1: USB-5PIN-CONN_USB-MINIB-MTH-POSTS; FCI_10033526; MPN 10033526-N3212MLF
JP3, JP4: SIP-12_2.54-SPACE-VERTICAL; HDRV12W63P254_12X1_3048X254H838; MPN TSW-150-07-T-S
JP5: SIP-2_2.54-SPACE-VERTICAL; HDRV2W63P254_2X1_508X254H838; MPN TSW-150-07-T-S
LED1: Red; LEDRD250W50D400H640_HS
LED2: Green; LEDRD250W50D400H640_HS
R2: 100K; RESAD1160W55L680D260_HS
R2C2: 143K; RESAD1160W55L680D260_HS
R3, R6: 470; RESAD770W45L370D210_HS
R4, R5: 68; RESAD770W45L370D210_HS
R7: 1.5K; RESAD770W45L370D210_HS
R8: 10K; RESAD770W45L370D210_HS
SET_VOLTAGE1: 0; RESAD770W45L370D210_HS
SW1: PUSHBUTTON-SHIELD-GND_CK_KMR211GLSR-TACTILE; CK_KMR211GLSR; MPN KMR211GLFS
U1: ATMEGA328-NO-THERMAL_32TQFP; QFP80P900X900X120-32L30HS; MPN ATMEGA328-AU
U3: ADJUSTABLE-VOLTAGE-REGULATOR_SOIC8; SOIC127P600X175-8L86HS; MPN MIC2951-03YM
Y1: 16MHz; MURATA_CTLS8_X_SERIES_HS

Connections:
A0: JP3.7, U1.23 (PC0(ADC0))
A1: JP3.8, U1.24 (PC1(ADC1))
A2: JP3.9, U1.25 (PC2(ADC2))
A3: JP3.10, U1.26 (PC3(ADC3))
A4: JP3.11, U1.27 (PC4(ADC4/SDA))
A5: JP3.12, U1.28 (PC5(ADC5/SCL))
A6: JP5.1, U1.19 (ADC6)
A7: JP5.2, U1.22 (ADC7)
AREF: C5.1, JP3.6, U1.20 (AREF)
D2: R4.1, U1.32 (PD2(INT0))
D3: JP4.9, U1.1 (PD3(INT1))
D4: JP4.8, U1.2 (PD4(XCK/T0))
D5: JP4.7, U1.9 (PD5(T1))
D6: JP4.6, U1.10 (PD6(AIN0))
D7: R5.1, U1.11 (PD7(AIN1))
D8: JP4.5, U1.12 (PB0(ICP))
D9: JP3.1, U1.13 (PB1(OC1A))
D10: JP3.2, U1.14 (PB2(SS/OC1B))
D11: JP3.3, U1.15 (PB3(MOSI/OC2))
D12: JP3.4, U1.16 (PB4(MISO))
D13: JP3.5, R6.1, U1.17 (PB5(SCK))
D+: D3.A, JP1.3 (D+), R4.2
D-: D4.A, JP1.2 (D-), R5.2, R7.1
DTR/RTS: C4.2, FTDI.6
GND: C3.2, C5.2, C7.2, D3.C, D4.C, FTDI.1, FTDI.2, J2.2, JP1.5 (GND), JP4.2, LED1.C, LED2.C, R2.1, SW1.1, SW1.4, SW1.5, U1.3 (GND), U1.5 (GND), U1.21 (GND), U3.4 (GND), Y1.2 (GND)
unnamed: LED1.A, R6.2
unnamed: U1.8 (PB7(XTAL2/TOSC2)), Y1.1 (OSC2)
unnamed: U1.7 (PB6(XTAL1/TOSC1)), Y1.3 (OSC1)
unnamed: LED2.A, R3.1
RST: C4.1, JP4.12, R8.2, SW1.2, SW1.3, U1.29 (PC6(/RESET))
RXD: FTDI.4, JP4.11, U1.30 (PD0(RXD))
TXD: FTDI.5, JP4.10, U1.31 (PD1(TXD))
VBAT: D6.A, J2.1, JP4.1
VBUS: D5.A, FTDI.3, JP1.1 (VBUS), JP4.3
VCC: C3.1, C6.1, JP4.4, R2C2.2, R3.2, R7.2, R8.1, SET_VOLTAGE1.2, U1.4 (VCC), U1.6 (VCC), U1.18 (AVCC), U3.1 (OUT)
VFB: C6.2, R2.2, R2C2.1, SET_VOLTAGE1.1, U3.7 (FEEDB)
VIN: C7.1, D5.C, D6.C, U3.8 (INPUT)

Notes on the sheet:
(from USB)
(from 6-29V battery)
Note: Case grounded
~ .25V forward drop each.
Note: NO Thermal

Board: 2 copper layers, 30 parts (0 on the bottom side), 37 nets, no tracks yet.

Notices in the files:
parts and their libraries:
SparkFun-Aesthetics: Licensing: CC v3.0 Share-Alike You are welcome to use this library for commercial purposes.
SparkFun-Resistors: Licensing: Creative Commons ShareAlike 4.0 International - https://creativecommons.org/licenses/by-sa/4.0
SparkFun-Aesthetics: Released under the Creative Commons
